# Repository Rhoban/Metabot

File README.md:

# The Metabot open-source quadruped robot

Metabot is an open-source DIY quadruped robotics platform. It can be 3D printed or
laser cutted (3mm acrylic).

Note that [the robot is now available as a kit](http://metabot.cc).
In this repository you will find all the open-source material to make (or hack) your own.

* [Bill of material](docs/bom.md)
* Mechanics
    * [3D Parts](mechanics/3d)
    * [Laser parts](mechanics/laser)
* [Electronics](electronics)
* [Firmware](firmware)
* [Joypad firmware](dfpad)

You can control the robot using the Metabot app (available on the Play Store)

[To get information about the previous robot version, see branch V1](https://github.com/Rhoban/Metabot/tree/v1)

## License

This project is under CC BY-NC license:
http://creativecommons.org/licenses/by-nc/3.0/

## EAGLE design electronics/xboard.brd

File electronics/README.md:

# Metabot electronics

Here are eagle schematics of the XBoard, the electronics inside the Metabot
robot.

## BOM

To assemble the board, you'll need the following components:

Name       | Farnell       | Quantity      | Description
-----------|---------------|---------------|--------------------------------------
MOLEX-53253-0370 | 1756921 | 4 | Connector for the motors
CD74HCT367M | 1739593 | 1 | Bus driver
1x20 0.1" header | 1593469 | 2 | Connector for the maple mini
1x8 0.1" header | 1593463 | 1 | Connector for the IMU
1x10 1mm header | 1109732 | 2 | Connector for the XBee
CEM-1203 | - | 1 | Buzzer
BC817 | 1081223RL | 1 | NPN transistor for the buzzer
EEE1CA470SP | 9696946 | 1 | 47uF decoupling capacitor
EEEFK1C221XP | 1850103 | 1 | 220uF decoupling capacitor
TS2940CW-3.3RP | 7261403RL | 1             | 3.3V Regulator
AP1117E50G-13 | 1825292RL  | 1             | 5V Regulator
LITTELFUSE  56000001009  | 1185363 | 1     | Fuse holder
Radial Fuse, 3.15A  37013150410 | 1716619 | 1 | Fuse
SUD50N04-8M8P-4GE3 | 1794799 | 1     | This big MOS can blow up the fuse programmatically
JST-BEC connector | - | 1 | Connector for the battery
R0805 22 ohms | - | 2 | 
R0805 470 ohms | - | 2 | 
R0805 1 Kohms | - | 1 |
R0805 4 Kohms | - | 3 |
R0805 10 Kohms | - | 1 |
R0805 20 Kohms | - | 1 |
C0805 100nF | - | 1 |

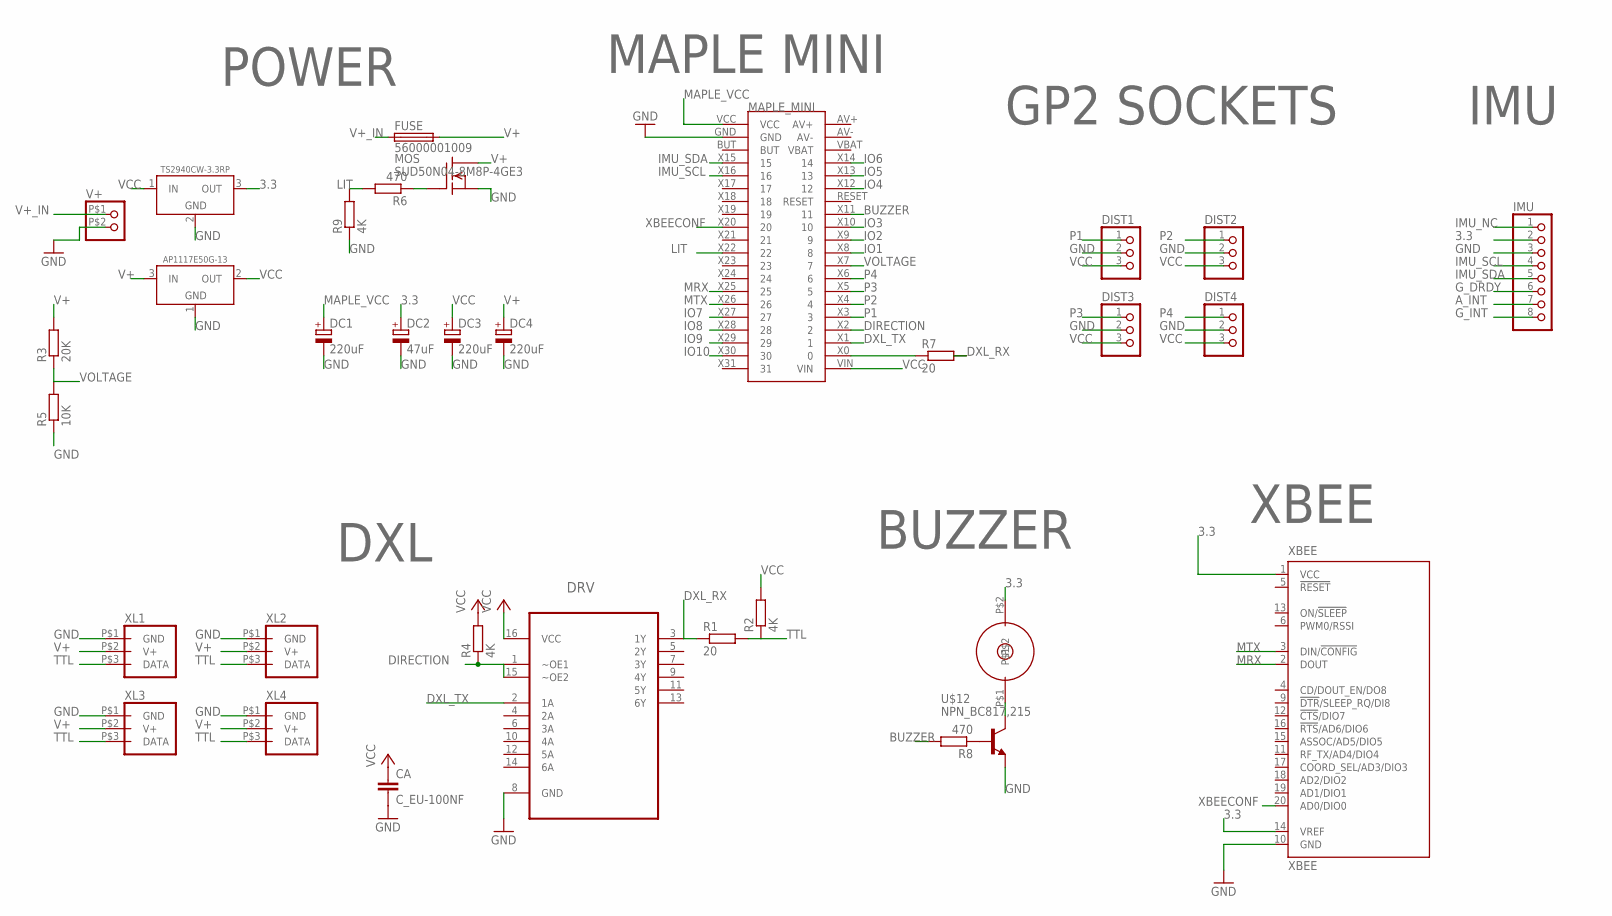
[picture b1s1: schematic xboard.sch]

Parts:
BUZZER: BUZZER10MM; BUZZER10
CA: C_EU-100NF; C0805
DC1, DC3, DC4: 220uF; PANASONIC_D8
DC2: 47uF; PANASONIC_D
DIST1, DIST2, DIST3, DIST4: CONNEC_1X03
DRV: CD74HCT367M; SOIC127P600X175-16N
FUSE: 56000001009
IMU: CONNEC_1X08
MAPLE_MINI: MAPLE_MINI; CONNEC_2X20
MOS: SUD50N04-8M8P-4GE3; TO252
R1, R7: 20; R0805
R2, R4, R9: 4K; R0805
R3: 20K; R0805
R5: 10K; R0805
R6, R8: 470; R0805
U$7: TS2940CW-3.3RP; SOT223
U$8: AP1117E50G-13; SOT223
U$12: NPN_BC817,215; SOT-23
V+: CONNEC_1X02BIG; CONNEC_1X02_BIG
XBEE: XBEE
XL1, XL2, XL3, XL4: XL_320_CONNEC; DXL_320_CONNEC

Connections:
3.3: BUZZER.P$2, DC2.+, IMU.2, U$7.3 (OUT), XBEE.1 (VCC), XBEE.14 (VREF)
A_INT: IMU.7
BUZZER: MAPLE_MINI.X11 (11), R8.2
DIRECTION: DRV.1 (~OE1), DRV.15 (~OE2), MAPLE_MINI.X2 (2), R4.1
DXL_RX: DRV.3 (1Y), R1.1, R7.2
DXL_TX: DRV.2 (1A), MAPLE_MINI.X1 (1)
GND: CA.2, DC1.-, DC2.-, DC3.-, DC4.-, DIST1.2, DIST2.2, DIST3.2, DIST4.2, DRV.8 (GND), IMU.3, MAPLE_MINI.GND, MOS.2 (S), R5.1, R9.1, U$7.2 (GND), U$8.1 (GND), U$12.2 (E), V+.P$2 (2), XBEE.10 (GND), XL1.P$1 (GND), XL2.P$1 (GND), XL3.P$1 (GND), XL4.P$1 (GND)
G_DRDY: IMU.6
G_INT: IMU.8
IMU_NC: IMU.1
IMU_SCL: IMU.4, MAPLE_MINI.X16 (16)
IMU_SDA: IMU.5, MAPLE_MINI.X15 (15)
IO1: MAPLE_MINI.X8 (8)
IO2: MAPLE_MINI.X9 (9)
IO3: MAPLE_MINI.X10 (10)
IO4: MAPLE_MINI.X12 (12)
IO5: MAPLE_MINI.X13 (13)
IO6: MAPLE_MINI.X14 (14)
IO7: MAPLE_MINI.X27 (27)
IO8: MAPLE_MINI.X28 (28)
IO9: MAPLE_MINI.X29 (29)
IO10: MAPLE_MINI.X30 (30)
LIT: MAPLE_MINI.X22 (22), R6.2, R9.2
MAPLE_VCC: DC1.+, MAPLE_MINI.VCC
MRX: MAPLE_MINI.X25 (25), XBEE.2 (DOUT)
MTX: MAPLE_MINI.X26 (26), XBEE.3 (DIN/!CONFIG)
unnamed: MOS.1 (G), R6.1
unnamed: MAPLE_MINI.X0 (0), R7.1
unnamed: R8.1, U$12.1 (B)
unnamed: BUZZER.P$1, U$12.3 (C)
P1: DIST1.1, MAPLE_MINI.X3 (3)
P2: DIST2.1, MAPLE_MINI.X4 (4)
P3: DIST3.1, MAPLE_MINI.X5 (5)
P4: DIST4.1, MAPLE_MINI.X6 (6)
TTL: R1.2, R2.1, XL1.P$3 (DATA), XL2.P$3 (DATA), XL3.P$3 (DATA), XL4.P$3 (DATA)
V+: DC4.+, FUSE.P$2 (2), MOS.3 (D), R3.2, U$8.3 (IN), XL1.P$2 (V+), XL2.P$2 (V+), XL3.P$2 (V+), XL4.P$2 (V+)
V+_IN: FUSE.P$1 (1), V+.P$1 (1)
VCC: CA.1, DC3.+, DIST1.3, DIST2.3, DIST3.3, DIST4.3, DRV.16 (VCC), MAPLE_MINI.VIN, R2.2, R4.2, U$7.1 (IN), U$8.2 (OUT)
VOLTAGE: MAPLE_MINI.X7 (7), R3.1, R5.2
XBEECONF: MAPLE_MINI.X20 (20), XBEE.20 (AD0/DIO0)

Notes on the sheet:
MAPLE MINI
GP2 SOCKETS
XBEE
DXL
POWER
IMU
BUZZER

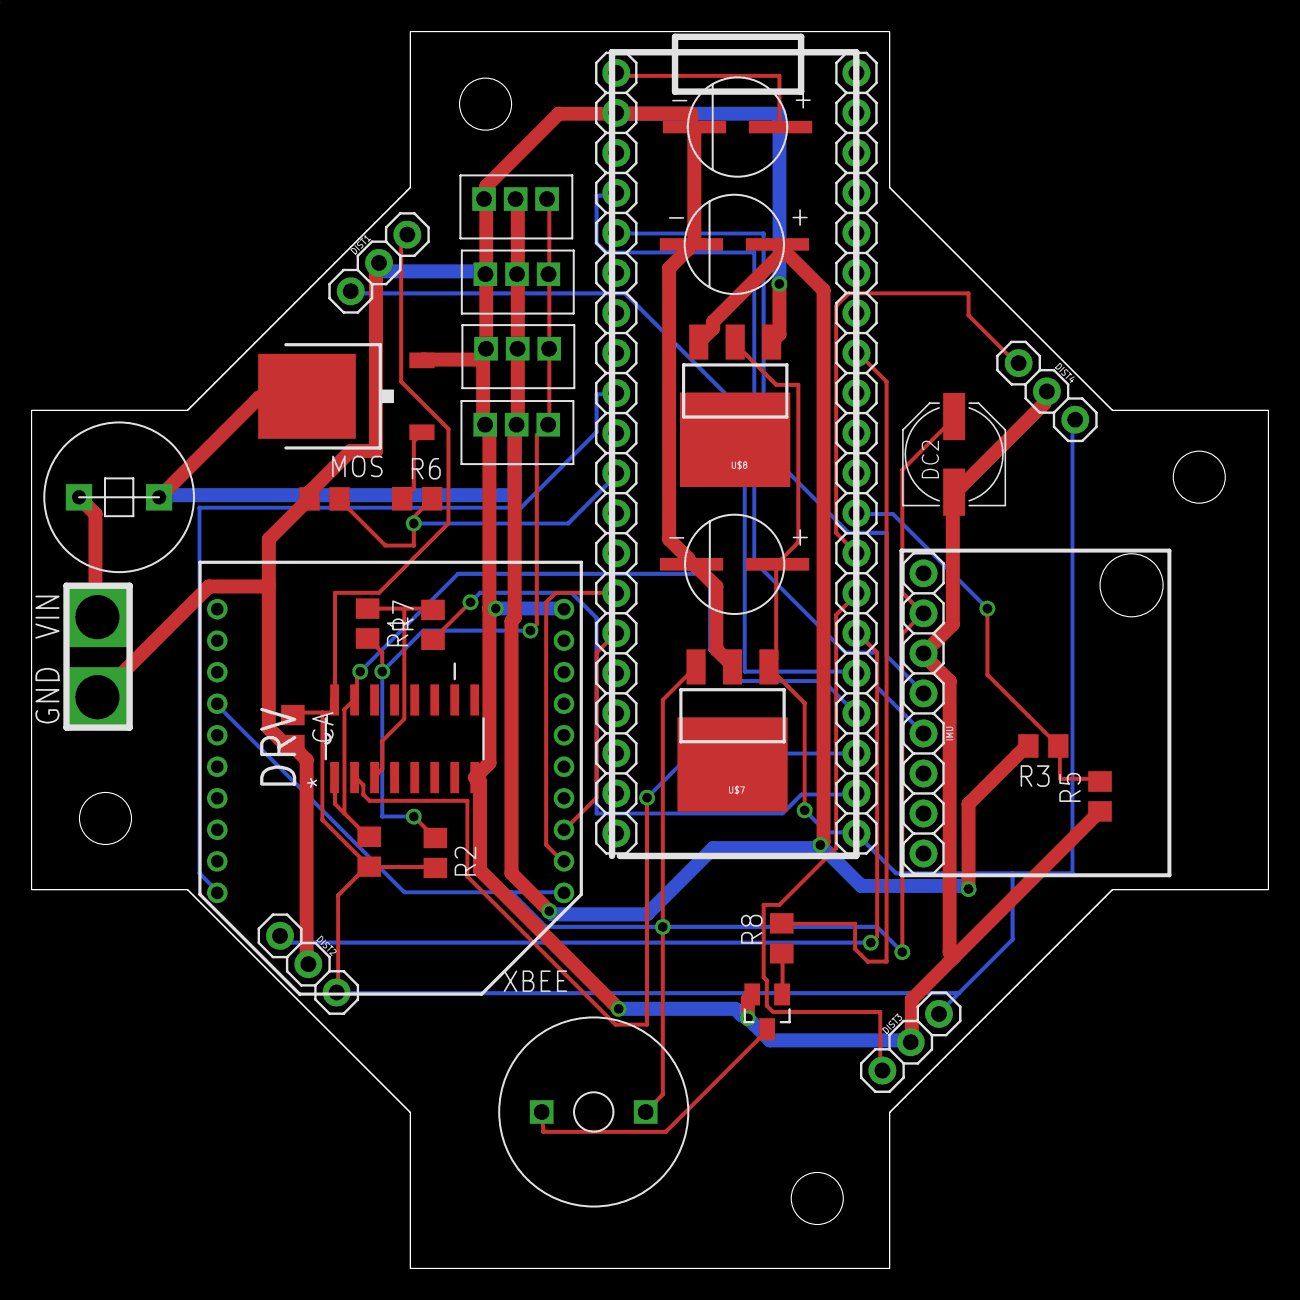
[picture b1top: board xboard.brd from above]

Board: 2 copper layers, 78.5 x 78.5 mm, 37 parts (0 on the bottom side), 26 nets.

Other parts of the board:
U$1, U$2, U$3, U$4: STAND-OFF

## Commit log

2014-12-06 Metabot
2014-12-06 Missing utils
2014-12-06 Cleaning & adding missing files
2014-12-06 Missing README+gitignore
2014-12-06 Updating docs
2014-12-06 Renaming spidey
2014-12-06 Removing unused files
2014-12-09 Changing br to 115200
2014-12-09 Fix screw bom
2014-12-09 Updating baudrate to maximum, adding toggle commands
2014-12-09 Voltage check
2014-12-11 Parts
2014-12-11 Body4
2014-12-11 Changing body bottom & top
2014-12-11 New battery fixation
2014-12-11 Images
2014-12-11 Fixing color
2014-12-11 Parts order
2014-12-11 Changing servoing, white legs
2014-12-11 order
2014-12-11 Fixing body4
2014-12-11 Body4 fixed
2014-12-11 Removing batfix
2014-12-12 Removing raspberry
2014-12-15 Adding version command
2014-12-16 Adding voltage as variable
2014-12-16 Updating bin
2014-12-16 Addng version
2014-12-16 Changing vendor:id
2014-12-17 Changing links to doc & demo
2014-12-18 Metabot.bin
2014-12-20 Adding plater.conf
2014-12-20 Moving to holes of 3 for Us
2014-12-23 Fixing website links
2015-01-27 Bolt trace
2015-01-27 Nuts traces
2015-01-28 Recompiled parts
2015-01-28 Adding 1mm height
2015-01-28 Body top
2015-02-19 JS-building
2015-02-21 Changing js script
2015-03-05 Including rhock (wip)
2015-03-06 Rhock support
2015-03-09 Fixing error in kill
2015-03-09 Reseting terminal on exiting rhock
2015-03-10 Updating Makefile according to RobotsWar
2015-03-12 FIxing js cmake
2015-03-12 Fixing directive name
2015-03-12 Rhock makefile
2015-03-16 Adding leds control and height
2015-03-17 Handling of start/stop
2015-03-17 Using ifdef
2015-03-17 Better handling of rhock-based process
2015-03-17 Not calling RESET stream
2015-03-18 Moved locomotion to motion
2015-03-18 Adding angles in rhock monitor
2015-03-18 Fixing motors colorize
2015-04-07 Adding natives
2015-04-07 Now using robot referential
2015-04-07 Adding rhock leg led
2015-04-10 Using speed instead of dx/dy
2015-04-23 Adding "started" command
2015-04-23 started=
2015-04-24 Adding remap=
2015-04-28 Fixing remap memory
2015-05-08 Re-enabling "old" splines
2015-05-08 js CMake
2015-05-09 Fixing missing atoi
2015-05-17 Reducing PID P
2015-05-22 Adding rhock natives
2015-05-22 Fixing ez
2015-05-22 New release of firmware
2015-05-22 Non-glitched splines
2015-05-22 Firmware
2015-06-02 adding 'version=' before the version number when firing the version command
2015-06-02 limiting depth to 1 in prepare.sh
2015-06-08 Adding rhock to prepare
2015-06-08 Fixing prepare.sh
2015-07-27 Adding buzzer
2015-07-27 Adding IMU
2015-07-27 Removing constant
2015-07-27 Adding accelerometer
2015-07-27 Adding distances sensors
2015-07-27 Buzzer impedance
2015-07-29 v2 first design
2015-07-29 Using static field to save ram
2015-07-29 Unused reply to save ram
2015-07-29 btconf
2015-07-29 Fixing voltage= for bc, fixing hysteresis
2015-07-29 Fixing bt-on reboot
2015-07-29 Fixing i2c errors check
2015-08-13 Removing FreeRTOS
2015-08-18 body
2015-09-08 Fixes
2015-09-16 Moving to re-tweaked Rhoban Maple env
2015-09-16 Checking RHOCK
2015-09-22 Adding model concept in makefile release
2015-09-22 Fixing dimensions
2015-09-27 Fixing RC
2015-09-27 Removing debug, yaw as a command
2015-11-27 Fixing master to use current Maple
2016-01-11 Hexabot variant
2016-01-20 V2 Mechanics
2016-02-08 Adding step command
2016-02-25 Adding buzzer beep
2016-02-25 crlf
2016-02-25 One distance sensor
2016-02-25 Fixing JS compile
2016-02-25 More permissive shut
2016-02-25 natives
2016-02-25 fixing buzzer_beep()
2016-02-25 native
2016-03-01 Mechanics (wip)
2016-03-01 V2 mechanics (wip)
2016-03-01 STLs
2016-03-01 Mechanics reorganization (laser+3d)
2016-03-01 Fixing the body 3D
2016-03-01 Fixing body gp2
2016-03-01 Updating STLs
2016-03-02 btconf repeat
2016-03-02 Adding IMU calibrate
2016-03-02 volt to centimeter for GP2
2016-03-02 Fixing r for V2
2016-03-03 Going back to RC when DTR is low
2016-03-03 Calib rot
2016-03-03 Reset packet
2016-03-03 Securing voltage alarm from user code
2016-03-03 Weight
2016-03-03 insist
2016-03-03 GP2 fixation, XBoard symetry
2016-03-03 More robust body top
2016-03-04 Removing useless information from monitoring
2016-03-04 Adding moving boolean
2016-03-04 Adding motion_is_moving()
2016-03-04 Simplification in motion
2016-03-07 Adding user controls
2016-03-07 Fixing controls native
2016-03-07 Adding extra x & y
2016-03-08 Reinitializing i2c on error
2016-03-24 holo
2016-03-30 Restoring tick
2016-04-06 XBoard schematics
2016-04-07 Fixing consistency
2016-04-23 New version
2016-04-25 Nops and mux
2016-04-25 holo wip
2016-04-25 Signal name place
2016-04-30 Opticals
2016-04-30 magn sens
2016-05-01 improving sound system
2016-05-01 Adding laser sizes
2016-05-04 autodesk
2016-05-09 Comportement animal
2016-05-10 Improving animal behaviour
2016-05-11 Delays in bt conf
2016-05-13 pulse
2016-05-13 6 leds (wip)
2016-05-13 New board
2016-05-15 parameters
2016-05-15 params
2016-05-15 Reducing p, voltage blink & stop
2016-05-15 proto
2016-05-19 Reducing p
2016-05-23 Penalty mode still not working
2016-05-27 Starting to implement penalty mode
2016-05-30 Penalty mode improving but still not functional, must find where does the wobble come from
2016-06-02 Better moving threshold on the controllers and in the robot firmware
2016-06-07 nops
2016-06-09 Adding reset command
2016-06-09 changing version number to 2.0
2016-06-10 merging
2016-06-10 tuning
2016-06-10 refactoring, mais il en reste
2016-06-11 LED nops
2016-06-11 adaptation motorisation nouveau proto
2016-06-11 testing led
2016-06-11 protection blocage moteur
2016-06-11 signal led pour blocage de roue
2016-06-12 stamina
2016-06-23 print ok when reset complete
2016-06-23 adding H after version to tell we're Holo
2016-06-24 version demo
2016-07-22 todo
2016-07-26 Buzzer 10mm
2016-10-28 laser
2016-10-28 side
2016-10-29 Config uniformisation
2016-10-29 uniformisation
2016-11-02 Distances
2016-11-02 Sizes
2016-11-02 Uniformisation joints
2016-11-02 DXFs, update.sh
2016-11-02 Fix leg
2016-11-02 Cubic splines
2016-11-03 Fixing motion rotation kinematics
2016-11-07 README
2016-11-07 summary
2016-11-07 XBoard
2016-11-07 elec
2016-11-07 README firwmare
2016-11-07 Metabot 2
2016-11-07 Back
2016-11-07 Install
2016-11-07 Firmware src
2016-11-07 Fixing js compilation
2016-11-17 Tab test
2016-11-17 BOM wip
2016-11-17 Head
2016-11-17 removing useless file
2016-11-17 Removing
2016-11-17 Fixing M3 nuts
2016-11-17 Magner precision
2016-11-17 Electronics BOM
2016-11-17 passives
2016-11-17 detail
2016-11-28 Beep simulation
2016-11-28 Adding odometry calibration defines
2016-11-28 Stopping buzzer on stop
2016-11-28 Stopping buzzer on all stop
2016-11-28 context controlling buzzer in rhock
2016-11-30 Blinking and stopping motors on voltage error
2016-11-30 Reading motors when disabled
2016-11-30 imu with simulation
2016-11-30 Binary release
2016-11-30 Fixing magn
2016-11-30 Boot melody
2016-11-30 Adding can start to prevent USB starting
2016-11-30 Documenting and cleaning
2016-11-30 Documentation
2016-11-30 Documenting terminal
2016-11-30 Extra angle
2016-11-30 Fixing beep
2016-11-30 Doc bt
2016-11-30 Killing user code in c ase of low voltage issue
2016-11-30 Sign
2016-12-01 Fixing btconf
2016-12-02 9600
2016-12-02 Laser prototype dimensions
2016-12-02 3D prototypes
2016-12-02 Fix define names
2016-12-02 Support for HM-12
2016-12-07 Updating BOM
2016-12-10 adding the other kind of GP2
2017-01-03 Side stronger
2017-01-03 Spacer
2017-01-05 BOM update
2017-02-09 Adding rhock functions, discounted distance, fixig bt mistake
2017-02-09 Adding yaw/pitch/roll and motor controls virtual machine natives
2017-02-10 Fixing stream API
2017-02-13 Process to ID motors w/ button
2017-02-13 Fixing button IDing
2017-02-13 Litting (wip)
2017-02-13 Board image
2017-02-13 fix link
2017-02-13 M3x15ish
2017-02-13 Fixing auto litting
2017-03-02 Update kinematic.h
    correct thr to the
2017-03-16 Fix prepare.sh
2017-03-22 Adding bluetooth one-touch config
2017-03-22 Adding dist one shot
2017-04-05 Comments
2017-04-05 Adding a convenient behavior.h/cpp +examples
2017-04-05 Disabling behavior by default
2017-04-05 Readme about behaviors
2017-05-15 Avoiding buzzer stop when stopping rhock programs when battery low
2017-05-15 Adding bhv in the terminal
2017-05-15 Moving leg phases outside the for loop
2017-05-15 Adding bhv in API
2017-05-15 Removing uselss variable
2017-05-17 Adding nameBT.sh
2017-05-17 Comment
2017-10-02 Robot drawing, cleaning up assembly alignment
2019-10-29 Enable DXL
2019-10-29 More delay in bat test
2019-10-29 Zero inflexion

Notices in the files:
parts and their libraries:
SparkFun-Electromechanical: Licensing: Creative Commons ShareAlike 4.0 International - https://creativecommons.org/licenses/by-sa/4.0
